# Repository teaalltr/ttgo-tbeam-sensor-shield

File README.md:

# Environmental sensor shield for the TTGO TBeam board

This project is OPEN HARDWARE

## Description

This is a shield for the ESP32 board TTGO TBeam v1.1 (with the AXP192), made specifically to connect some evironmental sensors, namely:

- the SPS30 particulate matter sensor ,
- a module for the BME680 
- the LPPYRA03AV pyranometer  
- the SEN0170 anemometer  
- a DCDC boost converter based on the MT3608 

The shield is connected to the SPS30 sensor via a [B5B-ZR(LF)(SN) thru-hole connector](https://www.digikey.it/product-detail/it/jst-sales-america-inc/B5B-ZR-LF-SN/455-1660-ND/926567) (the corresponding crimp terminal is the [ZHR-5](https://www.digikey.it/product-detail/it/jst-sales-america-inc/ZHR-5/455-1201-ND/608642) from JST).

Screw terminals are used, you can find them [here](https://www.amazon.it/gp/product/B07RR7D267/ref=ppx_yo_dt_b_asin_title_o03_s00?ie=UTF8&psc=1)

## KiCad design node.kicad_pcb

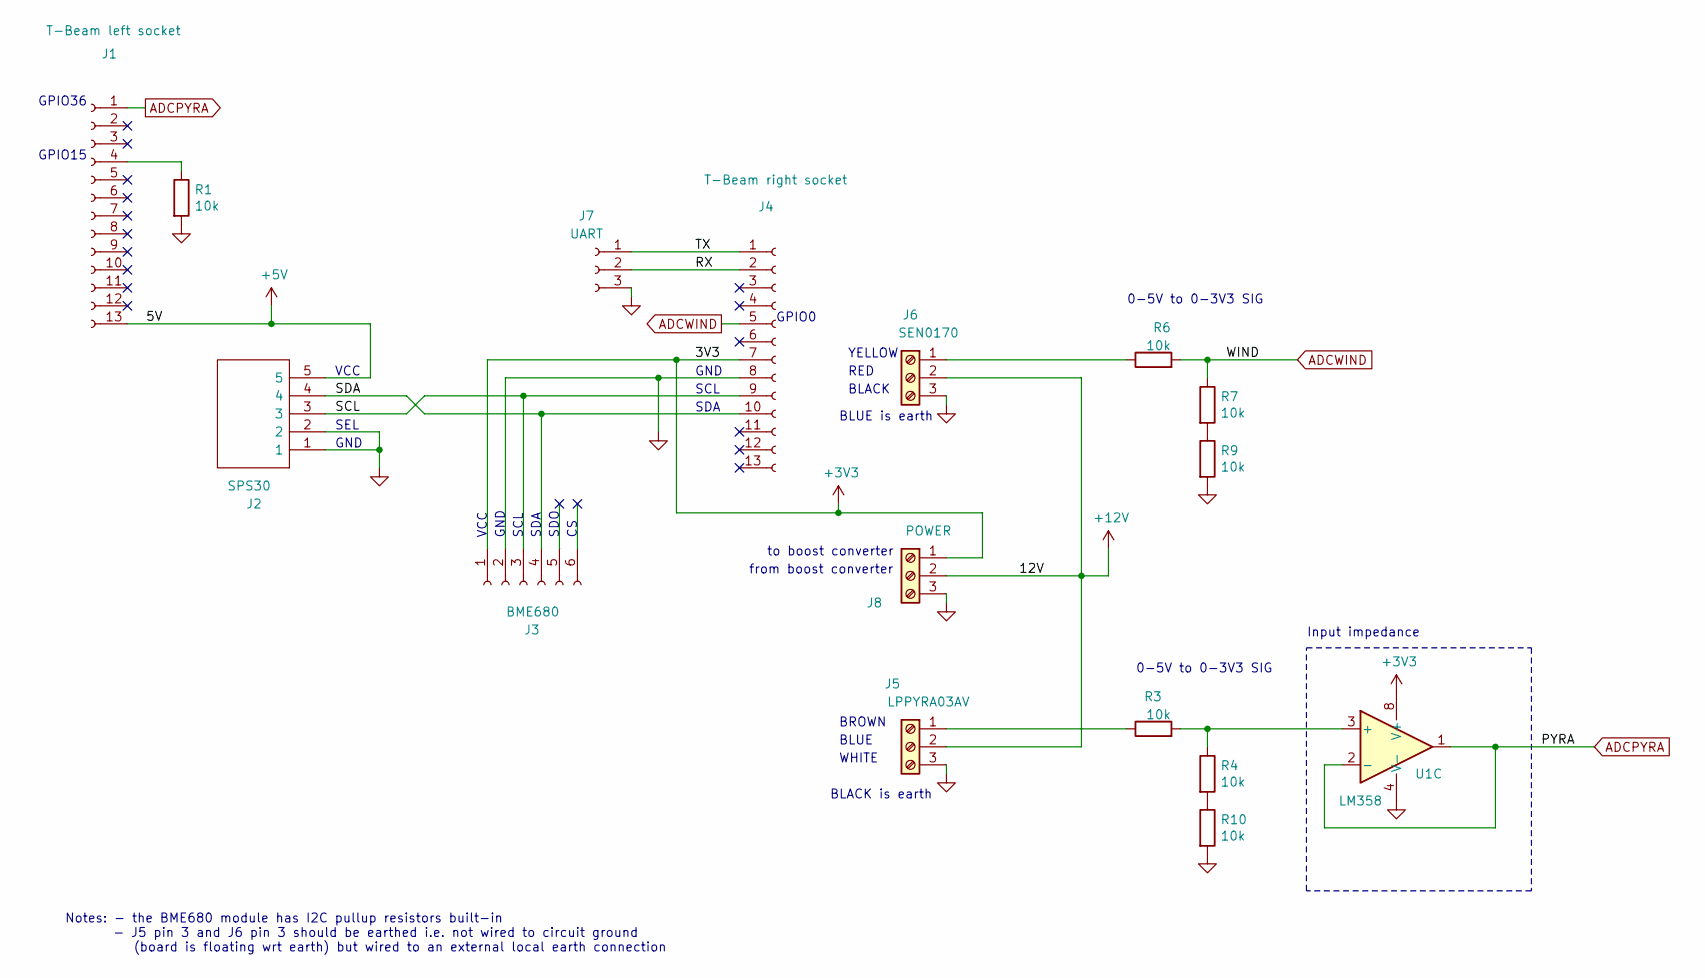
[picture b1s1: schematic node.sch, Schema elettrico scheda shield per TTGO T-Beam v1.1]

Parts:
J1: T-Beam left socket; PinSocket_1x13_P2.54mm_Vertical
J2: SPS30; SHDR5W50P0X150_1X5_900X350X450P; Manufacturer_Part_Number B5B-ZR (LF)(SN); Mouser Part Number N/A
J3: BME680; PinSocket_1x06_P2.54mm_Vertical
J4: T-Beam right socket; PinSocket_1x13_P2.54mm_Vertical
J5: LPPYRA03AV; TerminalBlock_RND_205-00277_1x03_P5.00mm_Vertical
J6: SEN0170; TerminalBlock_RND_205-00277_1x03_P5.00mm_Vertical
J7: UART; PinSocket_1x03_P2.54mm_Vertical
J8: POWER; TerminalBlock_RND_205-00277_1x03_P5.00mm_Vertical
R1, R3, R4, R6, R7, R9, R10: 10k; R_Axial_DIN0207_L6.3mm_D2.5mm_P10.16mm_Horizontal
U1: LM358; DIP-8_W7.62mm

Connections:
+3V3: J3.1, J4.7, J8.1, U1.8 (V+)
+5V: J1.13, J2.5
+12V: J5.2, J6.2, J8.2
/RX: J4.2, J7.2
/SCL: J2.3, J3.3, J4.9
/SDA: J2.4, J3.4, J4.10
/TX: J4.1, J7.1
ADCPYRA: J1.1, U1.1, U1.2 (-)
ADCWIND: J4.5, R6.2, R7.1
GND: J2.1, J2.2, J3.2, J4.8, J5.3, J6.3, J7.3, J8.3, R1.2, R9.2, R10.2, U1.4 (V-)
unnamed: J1.4, R1.1
unnamed: J5.1, R3.1
unnamed: J6.1, R6.1
unnamed: R3.2, R4.1, U1.3 (+)
unnamed: R7.2, R9.1
unnamed: R4.2, R10.1

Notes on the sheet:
Notes: - the BME680 module has I2C pullup resistors built-in - J5 pin 3 and J6 pin 3 should be earthed i.e. not wired to circuit ground (board is floating wrt earth) but wired to an external local earth connection
0-5V to 0-3V3 SIG
Input impedance
to boost converter
from boost converter
BLACK is earth
BROWN
SDA
SDO
SCL
GND
WHITE
GPIO0
BLUE is earth
RED
BLACK
YELLOW
BLUE
GPIO15
VCC
GPIO36
SEL

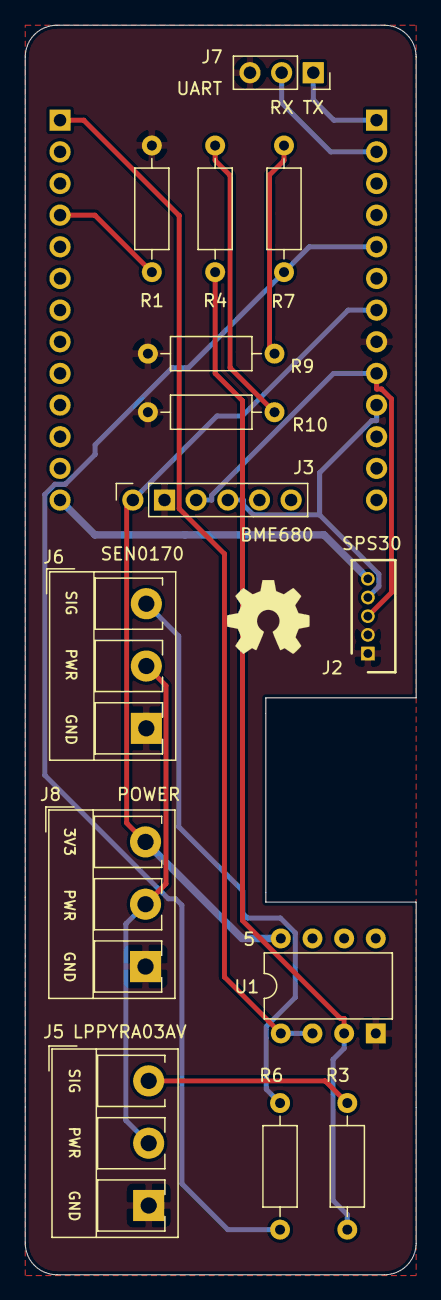
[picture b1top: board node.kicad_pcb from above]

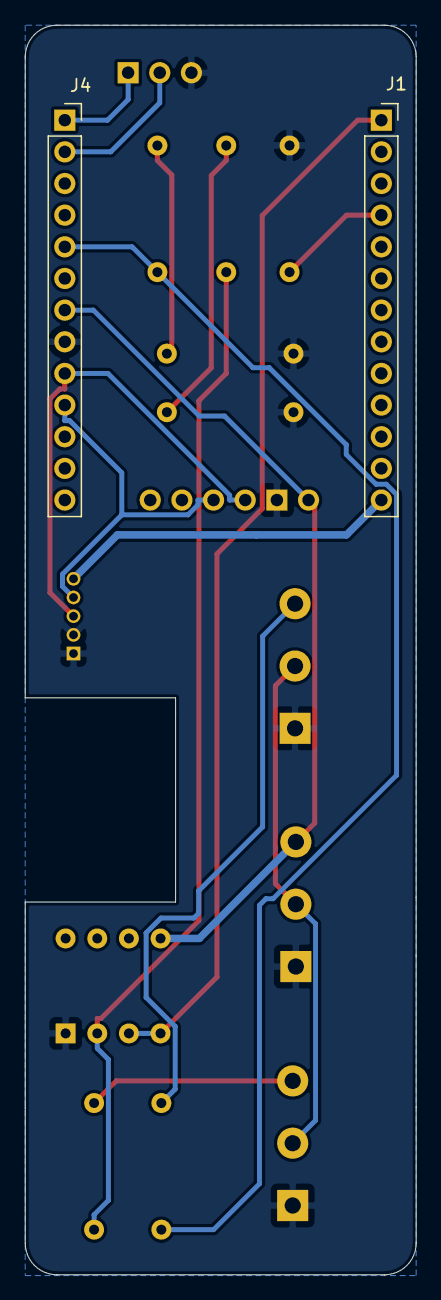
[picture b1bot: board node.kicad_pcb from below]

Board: 2 copper layers, 31.4 x 100.3 mm, 16 parts (2 on the bottom side), 16 nets.

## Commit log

2021-03-30 Initial drop
2021-03-30 add schematics pdf
2021-03-30 add PCB layers PDF

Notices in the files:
README.md:
licensebuttons by-nc-sa
